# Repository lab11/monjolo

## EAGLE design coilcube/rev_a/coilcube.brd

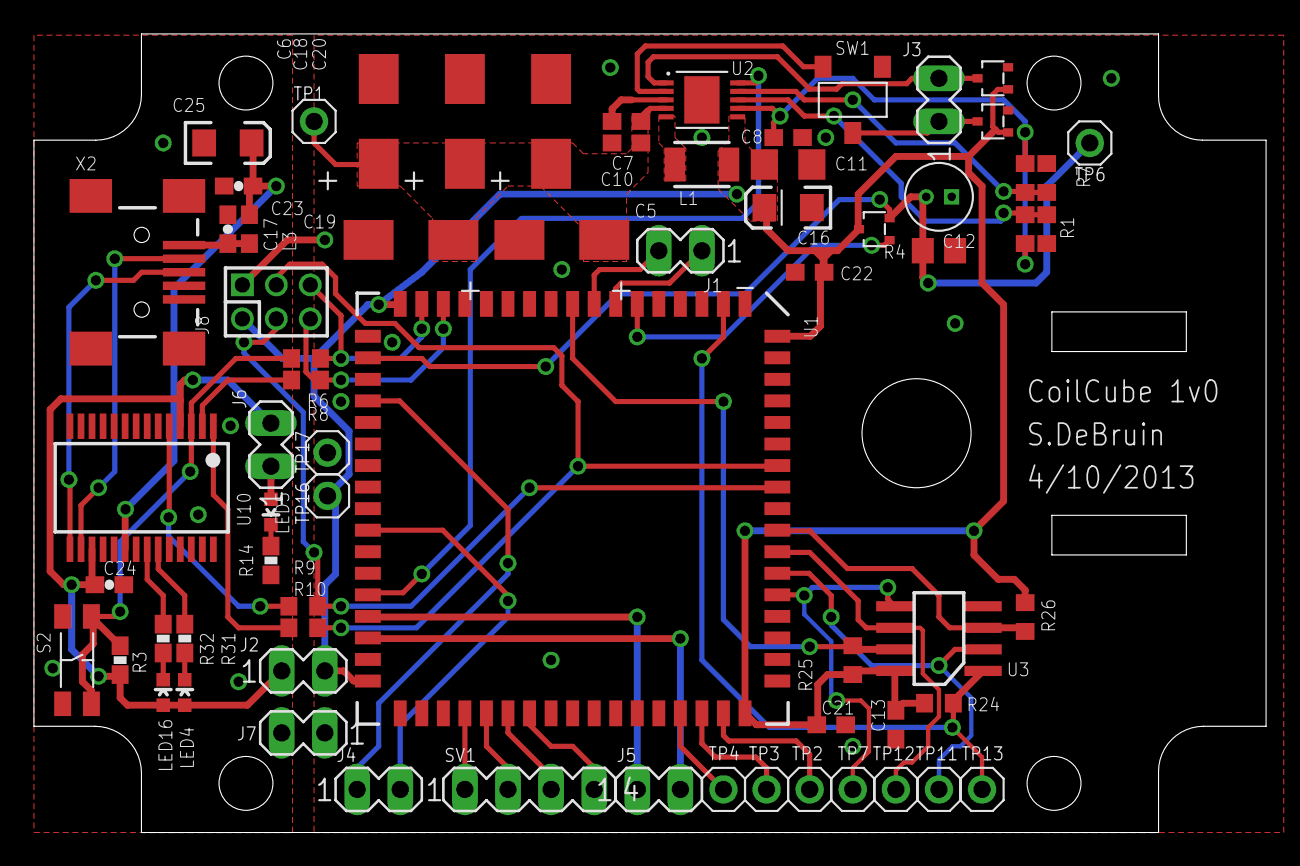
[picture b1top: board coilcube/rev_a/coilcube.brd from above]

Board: 2 copper layers, 72.6 x 47.1 mm, 69 parts (0 on the bottom side), 53 nets.

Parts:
C5, C6, C18, C19, C20: 100uF 25V; 2917_CAP_POL
C7: 1uF; C0603
C8: 4.7uF; C0603
C10, C13, C21, C22: 0.1uF; C0603
C11: 10uF; C1206
C12: 2.2uF; CPOL_EEA_1MM5
C16: 47uF; EIA3216
C17, C23, C24: 0603-CAP
C25: EIA3216
J1, J2, J3, J4, J5, J6, J7: MA02-1
J8: EPIC-PROG-PORT; HEADER2X3X2MM
L1: 10uH; 1210
L3: 0603
LED4, LED5, LED16: LED-0603
R1, R6, R7, R8, R9, R10: 0; R0603
R2, R5: NP; R0603
R3: 10k; 0603-RES
R4: 4.7M; R0805
R14, R31, R32: 240; 0603-RES
R24, R25, R26: 4.7k; R0603
S2: SWITCH-OFF-MOM
SV1: MA04-1
SW1: SWITCH_SPDP
T1, T2, T3: NCHAN_MOSFET
TP1: ORANGE; MA01-1
TP2, TP3, TP4, TP7, TP11, TP12: WHITE; MA01-1
TP6: BLUE; MA01-1
TP13: GREEN; MA01-1
TP16: RED; MA01-1
TP17: BLACK; MA01-1
U1: EPIC-CORE_A; EPIC-LCC68
U2: LTC3588_; MSOP-10-GNDPAD
U3: FM25LB; SOIC_8
U10: FT232RL; SSOP28
X2: USBSMD; USB-MINIB

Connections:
+3V3: C11.1, C13.1, C16.A, C21.1, C22.1, J2.2, J8.P$1, L1.2, R24.2, R25.2, R26.2, T1.G, T2.D, T3.G, TP16.1, U1.P$17, U1.P$34, U1.P$51, U1.P$68, U2.6, U3.P8
D0: R5.1, R7.1, U2.9
D1: R1.1, R2.1, U2.8
FRAM_CS: R24.1, TP13.1, U1.P$2, U3.P1
FRAM_HOLD: R25.1, U1.P$9, U3.P7
FRAM_WP: R26.1, U1.P$59, U3.P3
FTDIVDD: C24.1, J2.1, J6.2, LED4.A, LED16.A, R3.2, U10.4, U10.17
GND: C5.-, C6.-, C8.2, C10.2, C11.2, C12.-, C13.2, C16.C, C18.-, C19.-, C20.-, C21.2, C22.2, J7.1, J8.P$2, R2.2, R4.1, R7.2, SW1.P3, T1.S, T3.S, TP17.1, U1.P$1, U1.P$18, U1.P$35, U1.P$52, U2.GND, U3.P4
IGND: C17.2, C23.2, C24.2, C25.C, J7.2, R14.1, S2.P$1, S2.P$3, U10.7, U10.18, U10.21, U10.25, U10.26, X2.GND
MISO0: TP11.1, U1.P$57, U3.P2
MOSI0: TP7.1, U1.P$56, U3.P5
unnamed: J3.1, SW1.P2, T3.D
unnamed: J5.1, U1.P$31
unnamed: J5.2, U1.P$32
unnamed: J4.1, U1.P$21
unnamed: J4.2, U1.P$27
unnamed: SV1.4, U1.P$41
unnamed: SV1.3, U1.P$40
unnamed: SV1.2, U1.P$39
unnamed: SV1.1, U1.P$38
unnamed: TP2.1, U1.P$50
unnamed: J6.1, LED5.A
unnamed: TP3.1, U1.P$49
unnamed: TP4.1, U1.P$48
unnamed: L1.1, U2.5
unnamed: C7.2, U2.3
unnamed: J1.1, U1.P$7
unnamed: J1.2, U1.P$8
unnamed: LED5.C, R14.2
unnamed: U10.15, X2.D+
unnamed: U10.16, X2.D-
unnamed: LED4.C, R31.2
unnamed: LED16.C, R32.2
unnamed: R31.1, U10.23
unnamed: R32.1, U10.22
PGOOD: U1.P$30, U2.10
PZ1: J3.2, T1.D, U2.1
PZ2: SW1.P1, U2.2
RST: R3.1, R6.1, S2.P$2, S2.P$4, U10.3
RST-S: J8.P$6, R6.2, U1.P$16
RX1: R10.1, U10.1
RX1-S: J8.P$4, R10.2, U1.P$62
SCK0: TP12.1, U1.P$58, U3.P6
TCK: R8.1, U10.2
TCK-S: J8.P$5, R8.2, U1.P$15
TIME_CTL: T2.G, U1.P$6
TX1: R9.1, U10.5
TX1-S: J8.P$3, R9.2, U1.P$61
USBVCC1: C23.1, C25.A, L3.2, U10.20
VBUS1: C17.1, L3.1, X2.VBUS
VCAP: C5.+, C6.+, C7.1, C10.1, C18.+, C19.+, C20.+, TP1.1, U2.4
VIN2: C8.1, R1.2, R5.2, U2.7
VTIMER: C12.+, R4.2, T2.S, TP6.1, U1.P$19

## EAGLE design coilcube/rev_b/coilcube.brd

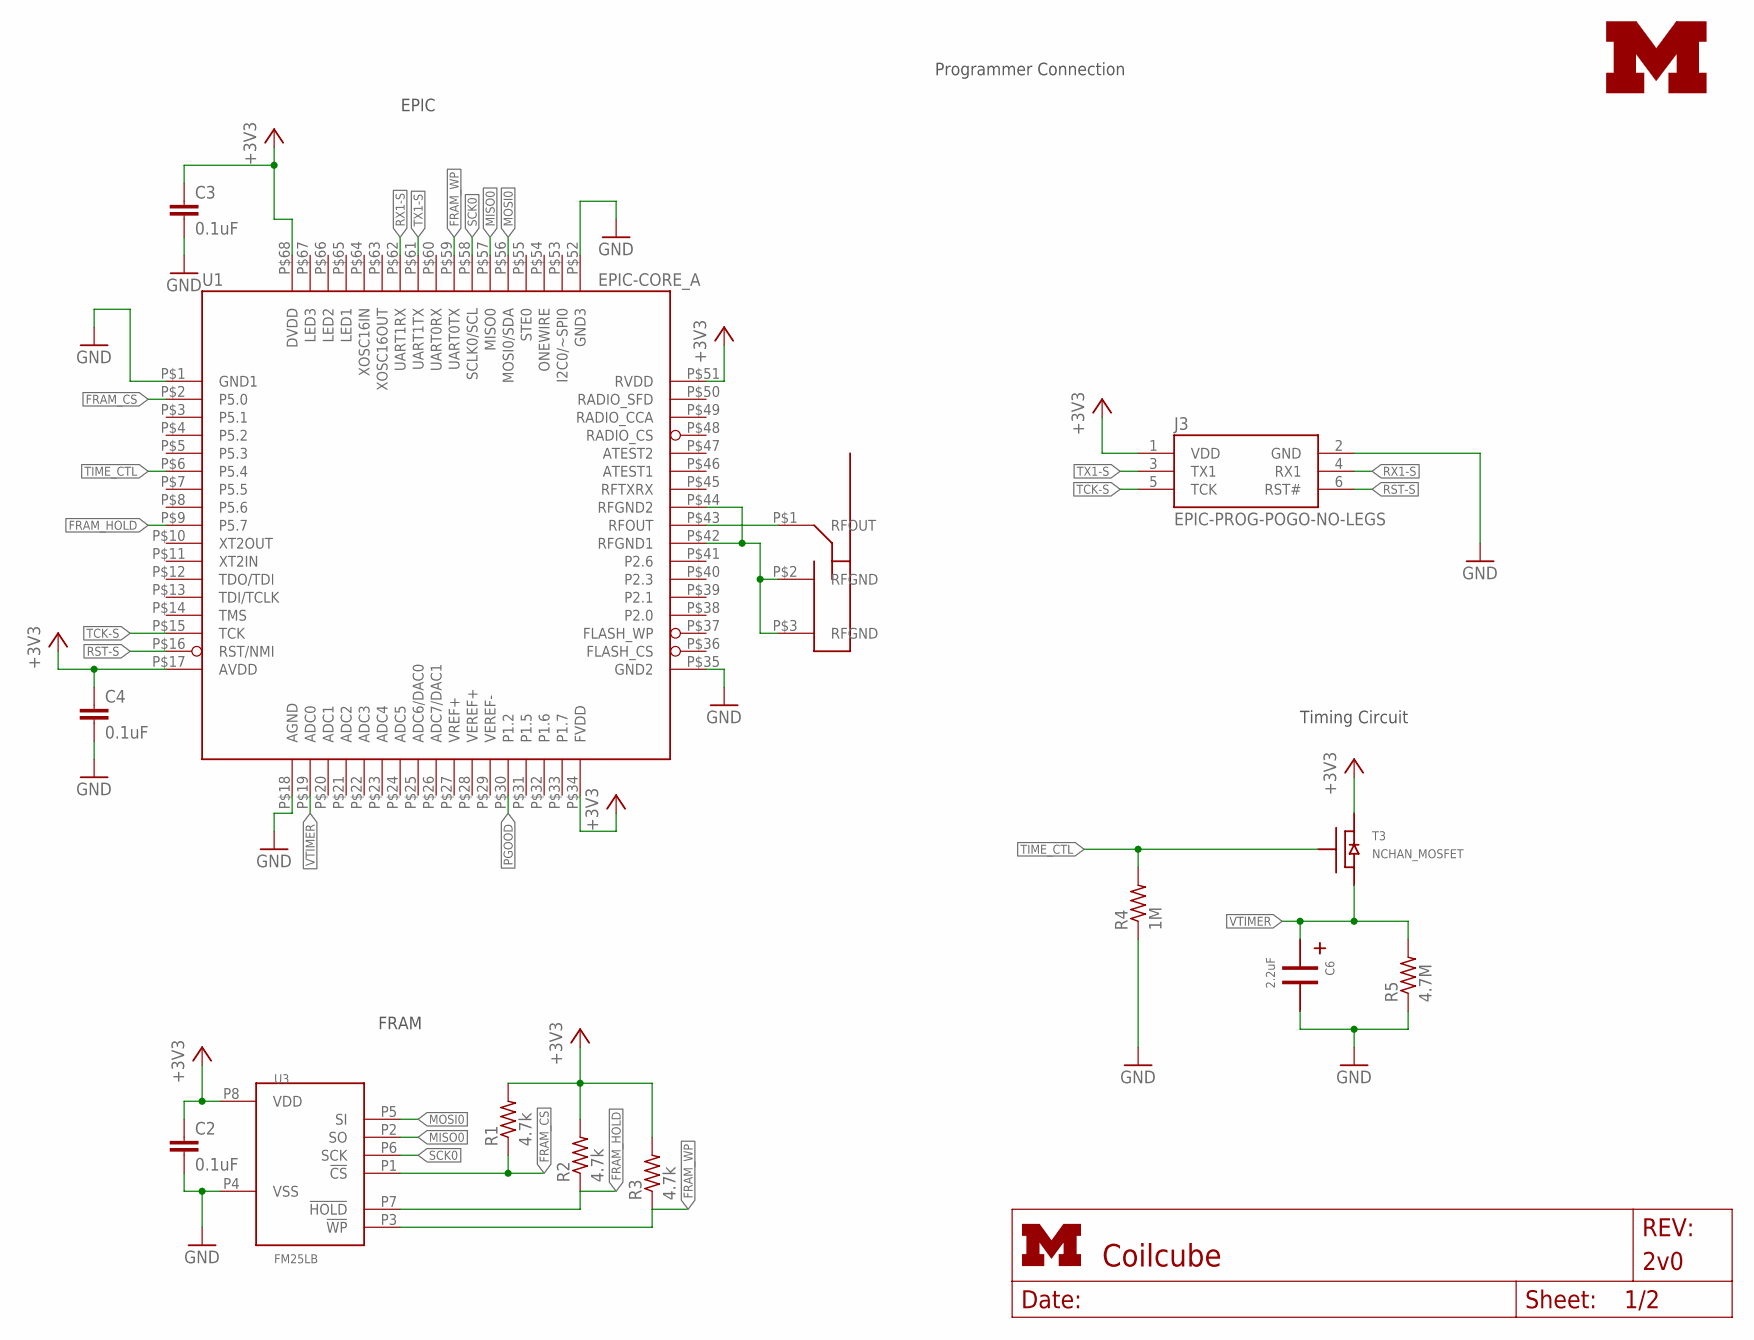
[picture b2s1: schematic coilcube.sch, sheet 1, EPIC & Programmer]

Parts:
ANT1: PIFA-2.4GHZ
C2, C3, C4: 0.1uF; C0603; DIGIKEY 445-1316-1-ND
C6: 2.2uF; CPOL_EEA_1MM5
J3: EPIC-PROG-POGO-NO-LEGS; TC2030-IDC-NL
R1, R2, R3: 4.7k; R0603; DIGIKEY P4.7KGCT-ND
R4: 1M; R0603; DIGIKEY RHM1.00MCFCT-ND
R5: 4.7M; R0603; DIGIKEY RHM4.7MCGDKR-ND
T3: NCHAN_MOSFET; DIGIKEY 568-3244-1-ND
U1: EPIC-CORE_A; EPIC-LCC68
U3: FM25LB; SOIC_8; DIGIKEY 428-3210-ND
U$1: UMICH_SOLID_MEDIUM; UMICH_SOLID_200MIL

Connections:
+3V3: C2.1, C3.1, C4.1, J3.1 (VDD), R1.2, R2.2, R3.2, T3.D, U1.P$17 (AVDD), U1.P$34 (FVDD), U1.P$51 (RVDD), U1.P$68 (DVDD), U3.P8 (VDD); also elsewhere on the board
FRAM_CS: R1.1, U1.P$2 (P5.0), U3.P1 (!CS)
FRAM_HOLD: R2.1, U1.P$9 (P5.7), U3.P7 (!HOLD)
FRAM_WP: R3.1, U1.P$59 (UART0TX), U3.P3 (!WP)
GND: C2.2, C3.2, C4.2, C6.-, J3.2 (GND), R4.1, R5.1, U1.P$1 (GND1), U1.P$18 (AGND), U1.P$35 (GND2), U1.P$52 (GND3), U3.P4 (VSS); also elsewhere on the board
MISO0: U1.P$57 (MISO0), U3.P2 (SO)
MOSI0: U1.P$56 (MOSI0/SDA), U3.P5 (SI)
unnamed: ANT1.P$1 (RFOUT), U1.P$43 (RFOUT)
PGOOD: U1.P$30 (P1.2); also elsewhere on the board
RFGND: ANT1.P$2 (RFGND), ANT1.P$3 (RFGND), U1.P$42 (RFGND1), U1.P$44 (RFGND2)
RST-S: J3.6 (RST#), U1.P$16 (RST/NMI); also elsewhere on the board
RX1-S: J3.4 (RX1), U1.P$62 (UART1RX); also elsewhere on the board
SCK0: U1.P$58 (SCLK0/SCL), U3.P6 (SCK)
TCK-S: J3.5 (TCK), U1.P$15 (TCK); also elsewhere on the board
TX1-S: J3.3 (TX1), U1.P$61 (UART1TX); also elsewhere on the board

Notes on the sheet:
Programmer Connection
EPIC
FRAM
Timing Circuit

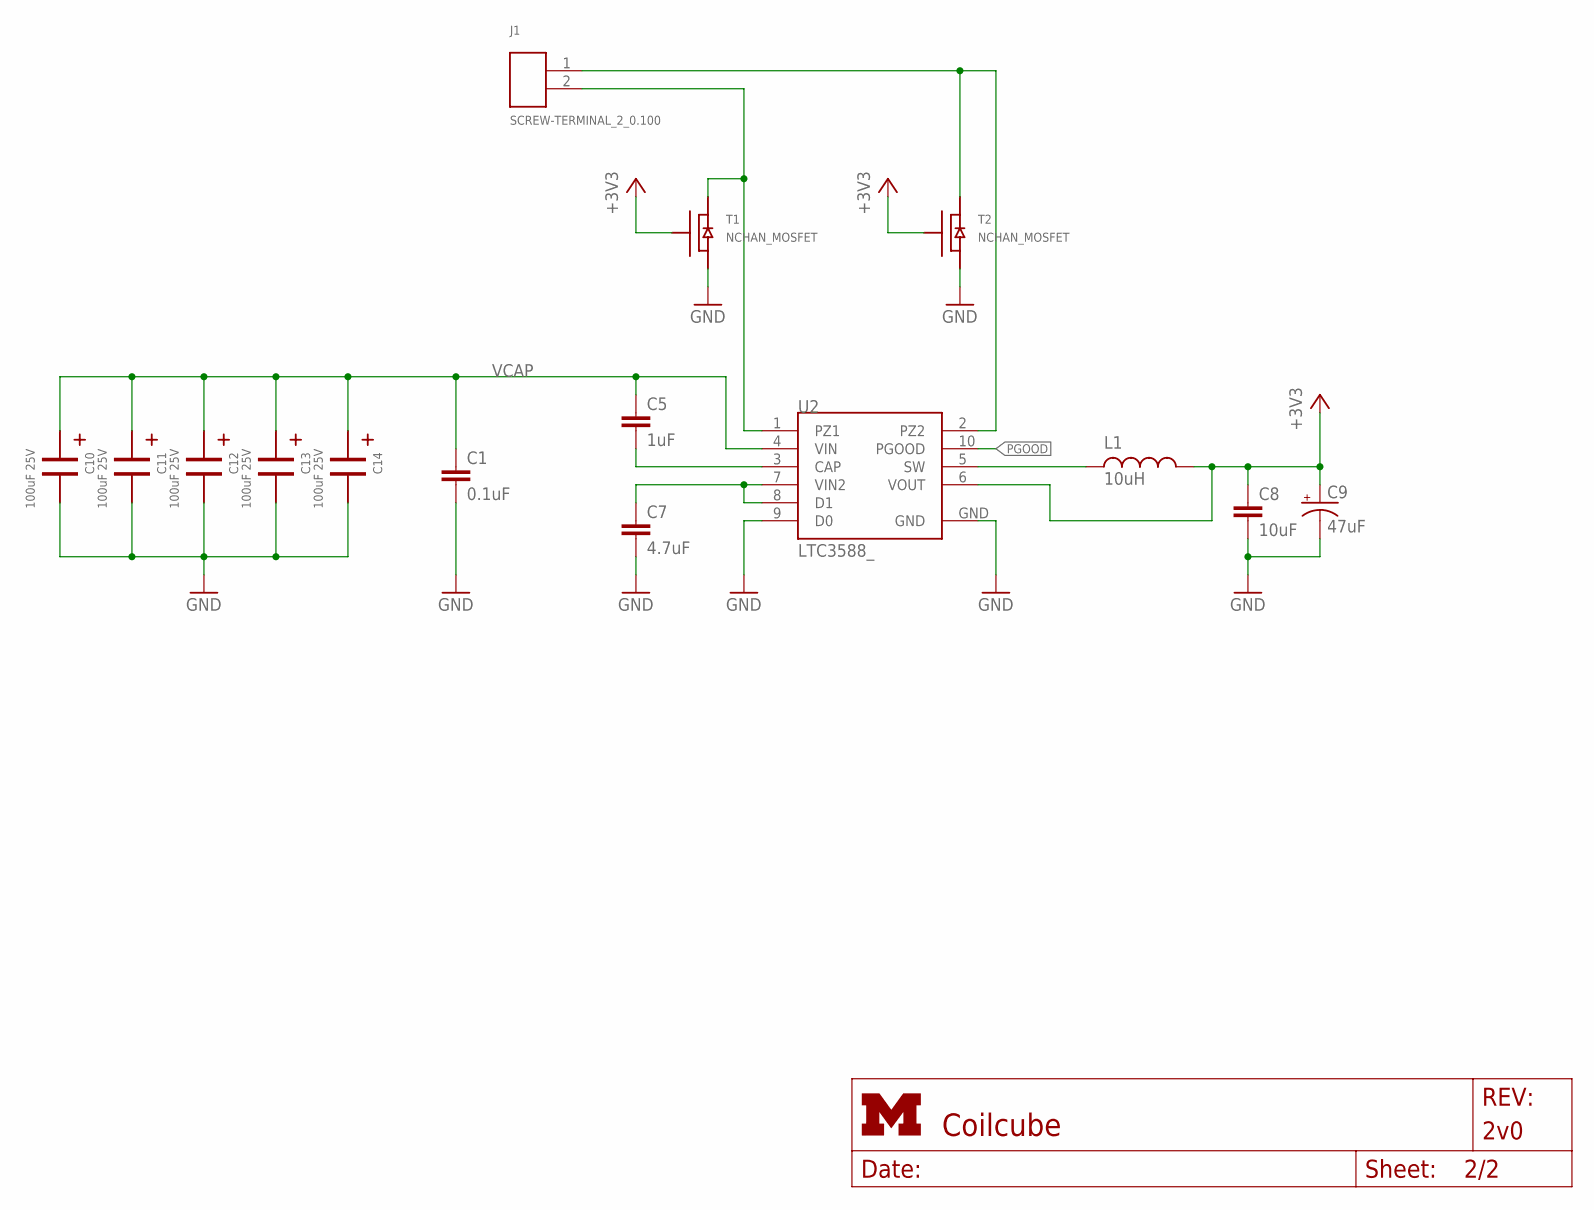
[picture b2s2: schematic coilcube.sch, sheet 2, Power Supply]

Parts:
C1: 0.1uF; C0603; DIGIKEY 445-1316-1-ND
C5: 1uF; C0603; DIGIKEY 445-1321-1-ND
C7: 4.7uF; C0603; DIGIKEY 445-5178-1-ND
C8: 10uF; C1206; DIGIKEY 399-8152-1-ND
C9: 47uF; EIA3216; DIGIKEY 399-3700-1-ND
C10, C11, C12, C13, C14: 100uF 25V; 2917_CAP_POL; DIGIKEY 399-5175-1-ND
J1: SCREW-TERMINAL_2_0.100; CONN_BLOCK_2
L1: 10uH; 1210; DIGIKEY 587-1625-1-ND
T1, T2: NCHAN_MOSFET; DIGIKEY SI1302DL-T1-GE3CT-ND
U2: LTC3588_; MSOP-10-GNDPAD; DIGIKEY LTC3588EMSE-1#PBF-ND

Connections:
+3V3: C8.1, C9.A (+), L1.2, T1.G, T2.G, U2.6 (VOUT); also elsewhere on the board
GND: C1.2, C7.2, C8.2, C9.C (-), C10.-, C11.-, C12.-, C13.-, C14.-, T1.S, T2.S, U2.9 (D0), U2.GND; also elsewhere on the board
unnamed: L1.1, U2.5 (SW)
unnamed: C5.2, U2.3 (CAP)
PGOOD: U2.10 (PGOOD); also elsewhere on the board
PZ1: J1.2, T1.D, U2.1 (PZ1)
PZ2: J1.1, T2.D, U2.2 (PZ2)
VCAP: C1.1, C5.1, C10.+, C11.+, C12.+, C13.+, C14.+, U2.4 (VIN)
VIN2: C7.1, U2.7 (VIN2), U2.8 (D1)

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
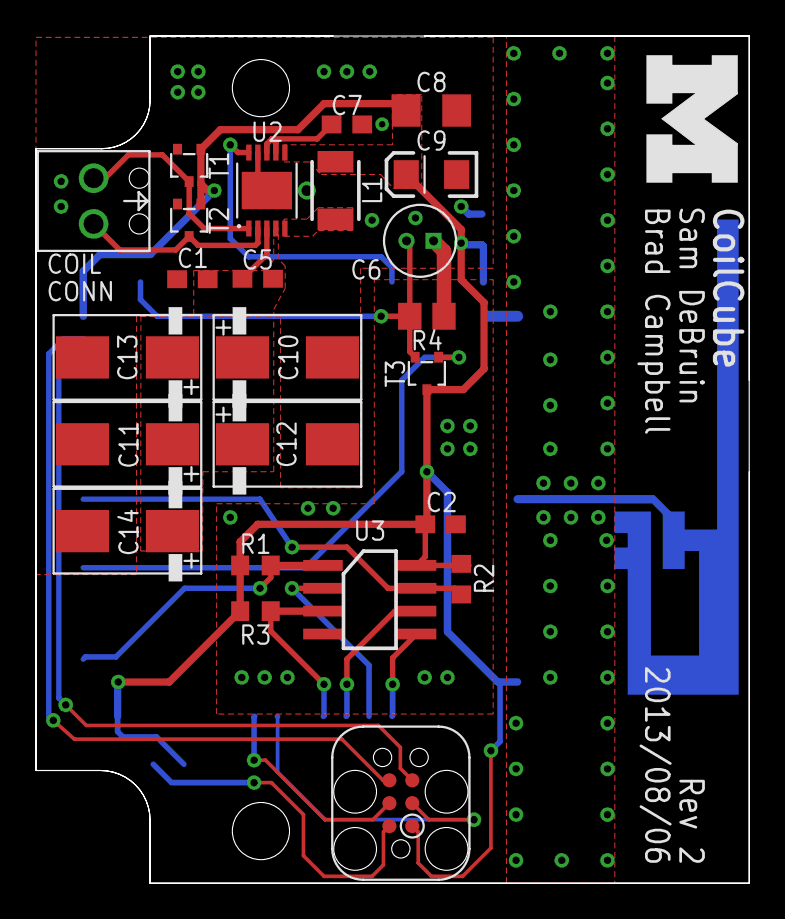
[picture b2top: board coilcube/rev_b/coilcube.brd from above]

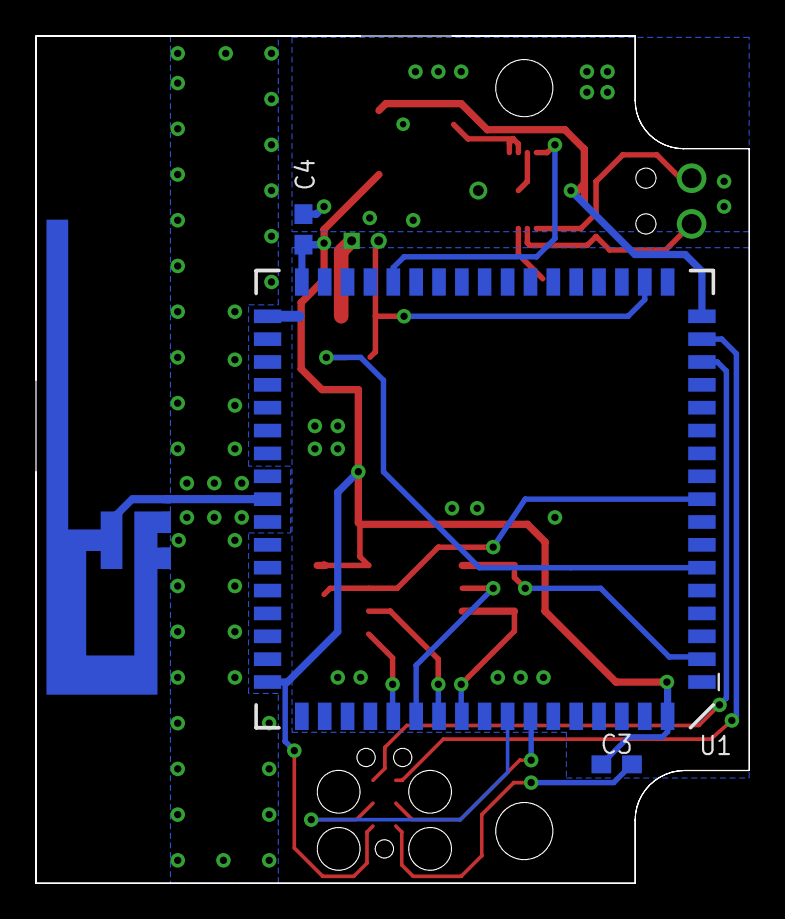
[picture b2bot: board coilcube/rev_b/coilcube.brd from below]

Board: 2 copper layers, 39.6 x 47.1 mm, 29 parts (4 on the bottom side), 23 nets.

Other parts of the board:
J2: TC2030-IDC

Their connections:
+3V3: J2.1; also elsewhere on the board
GND: J2.2; also elsewhere on the board
RST-S: J2.6; also elsewhere on the board
RX1-S: J2.4; also elsewhere on the board
TCK-S: J2.5; also elsewhere on the board
TX1-S: J2.3; also elsewhere on the board

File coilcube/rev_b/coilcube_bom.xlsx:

Qty | Value | Device | Package | Parts | Description | DIGIKEY
4 | 0.1uF | C-EUC0603 | C0603 | C1, C2, C3, C4 | CAPACITOR, European symbol | 445-1316-1-ND
1 | 1uF | C-EUC0603 | C0603 | C5 | CAPACITOR, European symbol | 445-1321-1-ND
1 | 2.2uF | CAP_POLEA1MM5 | CPOL_EEA_1MM5 | C6 |  | P14506-ND
1 | 4.7uF | C-EUC0603 | C0603 | C7 | CAPACITOR, European symbol | 445-5178-1-ND
1 | 10uF | C-EUC1206 | C1206 | C8 | CAPACITOR, European symbol | 399-8152-1-ND
1 | 47uF | CAP_POL1206 | EIA3216 | C9 | Capacitor Polarized | 399-3700-1-ND
5 | 100uF 25V | 2917_CAP_POL | 2917_CAP_POL | C10, C11, C12, C13, C14 |  | 399-5175-1-ND
1 | SCREW-TERMINAL_2_0.100 | SCREW-TERMINAL_2_0.100 | CONN_BLOCK_2 | J1 | 2x 0.100 in screw terminal block | 277-1273-ND
1 | 10uH | INDUCTOR1210 | 1210 | L1 | Inductors | 587-1625-1-ND
3 | 4.7k | R-US_R0603 | R0603 | R1, R2, R3 | RESISTOR, American symbol | P4.7KGCT-ND
1 | 4.7M | R-US_R0805 | R0805 | R4 | RESISTOR, American symbol | P4.7MACT-ND
2 | NCHAN_MOSFET | NCHAN_MOSFET | NCHAN_MOSFET | T1, T2 |  | SI1302DL-T1-GE3CT-ND
1 | NCHAN_MOSFET | NCHAN_MOSFET | NCHAN_MOSFET | T3 |  | 568-3244-1-ND
1 | EPIC-CORE_A | EPIC-CORE_A | EPIC-LCC68 | U1
1 | LTC3588_ | LTC3588_ | MSOP-10-GNDPAD | U2 | Energy Harvesting Power Supply | LTC3588EMSE-1#PBF-ND
1 | FM25LB | FM25LB | SOIC_8 | U3 |  | 428-3210-ND

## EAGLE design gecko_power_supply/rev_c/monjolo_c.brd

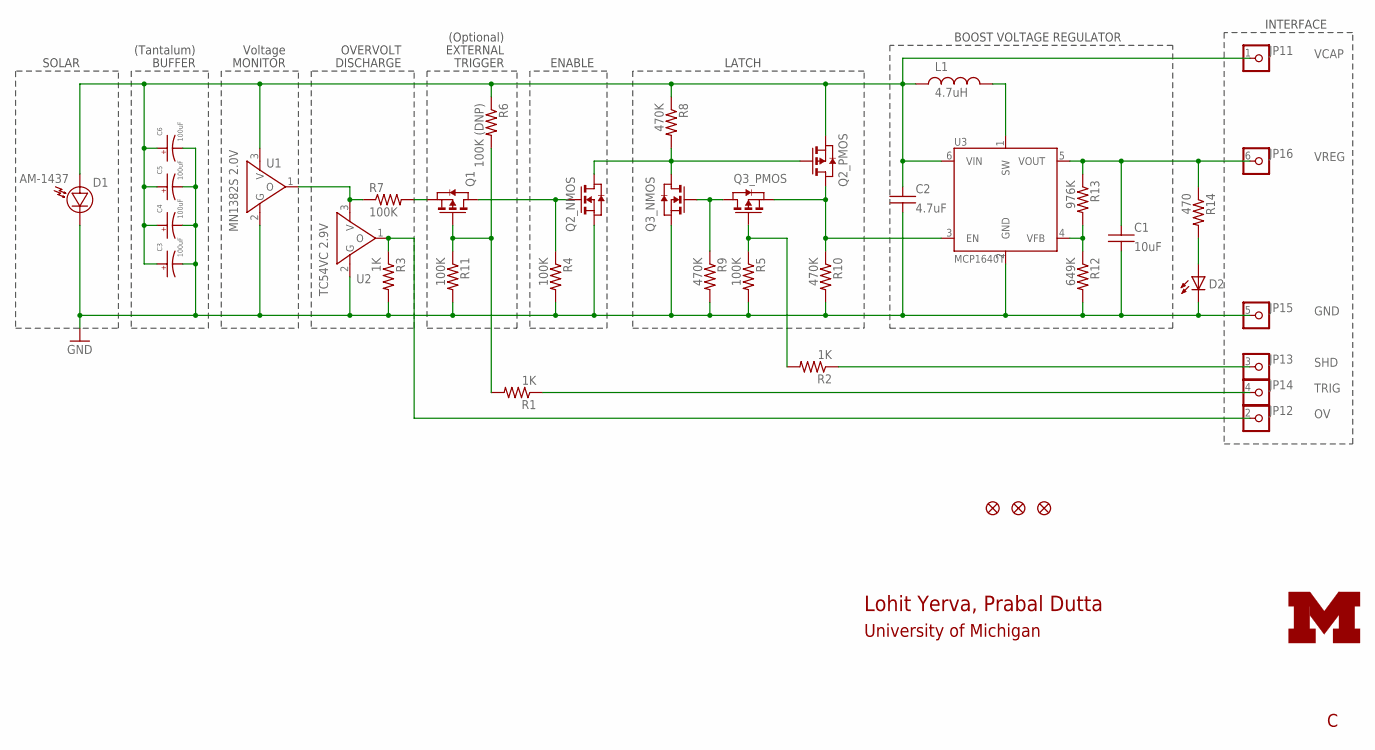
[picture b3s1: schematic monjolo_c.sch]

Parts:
C1: 10uF; R0603B
C2: 4.7uF; R0603B
C3, C4, C5, C6: 100uF; CAP1210
D1: AM-1437
D2: LED0603; LED-0603
JP1: PINHD6; HD6
JP2, JP3, JP4: FIDUCIAL1X2; FIDUCIAL-1X2
L1: 4.7uH; L2828
Q1: PMOSSOT23; SOT-23
Q2, Q3: DUAL_MOSFET_NP; TSOP-6
R1, R2, R3: 1K; R0603B
R4, R5, R7, R11: 100K; R0603B
R6: 100K (DNP); R0603B
R8, R9, R10: 470K; R0603B
R12: 649K; R0603B
R13: 976K; R0603B
R14: 470; R0603B
U1: MN1382S 2.0V; MINI-3DC
U2: TC54VC 2.9V; MINI-3DC
U3: MCP1640T; SOT-23-6
U$1: UMICH_SOLID_SMALL; UMICH_SOLID_75MIL

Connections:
GND: C1.2, C2.2, C3.ANODE, C4.ANODE, C5.ANODE, C6.ANODE, D1.- (C), D2.C, JP1.5, Q2.5 (S), Q3.5 (S), R3.2, R4.2, R5.2, R9.2, R10.2, R11.2, R12.2, U1.2 (G), U2.2 (G), U3.2 (GND)
unnamed: R12.1, R13.2, U3.4 (VFB)
unnamed: Q1.2 (S), R7.2
unnamed: L1.2, U3.1 (SW)
unnamed: D2.A, R14.2
unnamed: Q3.1 (G), Q3.4 (D), R9.1
unnamed: Q1.1 (D), Q2.1 (G), R4.1
unnamed: JP1.3, R2.1
unnamed: Q2.3 (G), Q2.6 (D), Q3.6 (D), R8.2
unnamed: Q3.3 (G), R2.2, R5.1
unnamed: JP1.2, R3.1, U2.1 (O)
unnamed: R7.1, U1.1 (O), U2.3 (V)
unnamed: Q1.3 (G), R1.2, R6.2, R11.1
unnamed: JP1.4, R1.1
unnamed: Q2.4 (D), Q3.2 (S), R10.1, U3.3 (EN)
VCAP: C2.1, C3.CATHODE, C4.CATHODE, C5.CATHODE, C6.CATHODE, D1.+ (A), JP1.1, L1.1, Q2.2 (S), R6.1, R8.1, U1.3 (V), U3.6 (VIN)
VREG: C1.1, JP1.6, R13.1, R14.1, U3.5 (VOUT)

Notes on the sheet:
Lohit Yerva, Prabal Dutta
VCAP
VREG
GND
SHD
TRIG
University of Michigan
SOLAR
(Tantalum)
BUFFER
Voltage
MONITOR
OVERVOLT
DISCHARGE
EXTERNAL
TRIGGER
(Optional)
ENABLE
LATCH
BOOST VOLTAGE REGULATOR
INTERFACE

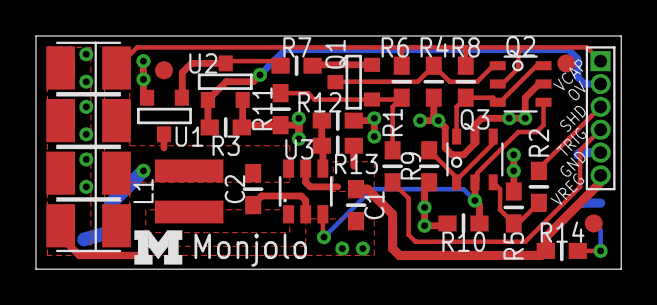
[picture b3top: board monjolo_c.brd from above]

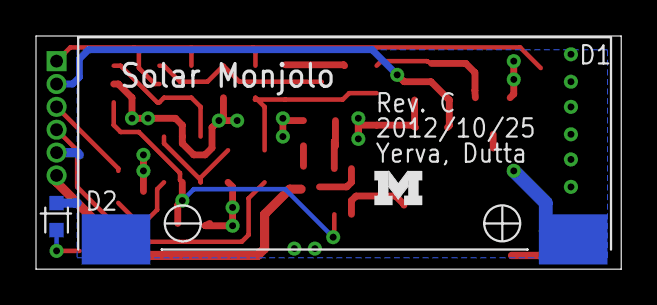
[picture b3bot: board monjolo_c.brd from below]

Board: 2 copper layers, 32.5 x 13.0 mm, 35 parts (3 on the bottom side), 17 nets.

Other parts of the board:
U$3: UMICH_SOLID_SMALL; UMICH_SOLID_75MIL

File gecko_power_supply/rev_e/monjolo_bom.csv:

# Bill of Materials
# Converted from monjolo_bom.xls
# Generated by bom_to_text.py

Qty,Value,Layout,Parts,Digikey Part #,DIGIREEL,Coilcraft,Discription,Notes
1,10uF,C0603,C1,445-7486-1-ND,445-7486-6-ND,,CAP CER 10UF 10V 10% X5R 0603,
1,4.7uF,C0603,C2,490-6407-1-ND,490-6407-6-ND,,CAP CER 4.7UF 6.3V 10% X5R 0603,
4,100uF,C1206,"C3, C4, C5, C6, C7",478-3130-1-ND,478-3130-6-ND,,CAP TANT 100UF 6.3V 20% 1210,
1,AM-1417,Solar cell,D1,869-1000-ND,,,SOLAR CELL AM 35MM X 13.9MM,
1,LED,LED0603,D2,160-1837-1-ND,160-1837-6-ND,,LED BLUE CLEAR 0603 SMD,
1,4.7uH,L-US,L1,,,EPL3012-472MLB,4.7 UH INDUCTOR,
1,PMOS,SOT23-3,Q1,SI2305ADS-T1-GE3CT-ND,SI2305ADS-T1-GE3DKR-ND,,MOSFET P-CH 8V 5.4A SOT23-3,
2,MOSFET NP-CH,6-TSOP,"Q2, Q3",SI3585DV-T1-E3CT-ND,SI3585DV-T1-E3DKR-ND,,MOSFET N/P-CH 20V 2A/1.5A 6-TSOP,
3,1K,R0603,"R1, R2, R3",RHM1.00KCFCT-ND,RHM1.00KCFDKR-ND,,RES 1.00K OHM 1/10W 1% 0603 SMD,
4,100K,R0603,"R4, R5, R7, R11",RHM100KCFCT-ND,RHM100KCFDKR-ND,,RES 100K OHM 1/10W 1% 0603 SMD,
DNP,100K,R0603,R6,RHM100KCFCT-ND,RHM100KCFDKR-ND,,RES 100K OHM 1/10W 1% 0603 SMD,To use External Trigger solder R6 instead of R11
3,470K,R0603,"R8, R9, R10",RHM470KCFCT-ND,RHM470KCFDKR-ND,,RES 470K OHM 1/10W 1% 0603 SMD,
1,649K,R0603,R12,541-649KHCT-ND,541-649KHDKR-ND,,RES 649K OHM 1/10W 1% 0603 SMD,
1,976K,R0603,R13,541-976KHCT-ND,541-976KHDKR-ND,,RES 976K OHM 1/10W 1% 0603 SMD,
1,470,R0603,R14,RHM470CFCT-ND,RHM470CFDKR-ND,,RES 470 OHM 1/10W 1% 0603 SMD,
1,MN1382S 2.0V,SOT23-3,U1,TC54VC2102ECB713CT-ND,TC54VC2102ECB713DKR-ND,,IC VOLT DETECT 2.0V CMOS SMD,
1,TC54VC 2.9V,SOT23-3,U2,TC54VC2902ECB71CT-ND,TC54VC2902ECB71DKR-ND,,IC VOLT DETECTOR 2.9V SOT23A,Not needed if not using external Trigger (R11 soldered)
1,MCP1640T,SOT23-6,U3,MCP1640T-I/CHYCT-ND,MCP1640T-I/CHYDKR-ND,,IC BOOST SYNC ADJ 0.1A SOT23-6,

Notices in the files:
parts and their libraries:
SparkFun-PowerIC: Licensing: CC v3.0 Share-Alike You are welcome to use this library for commercial purposes.
